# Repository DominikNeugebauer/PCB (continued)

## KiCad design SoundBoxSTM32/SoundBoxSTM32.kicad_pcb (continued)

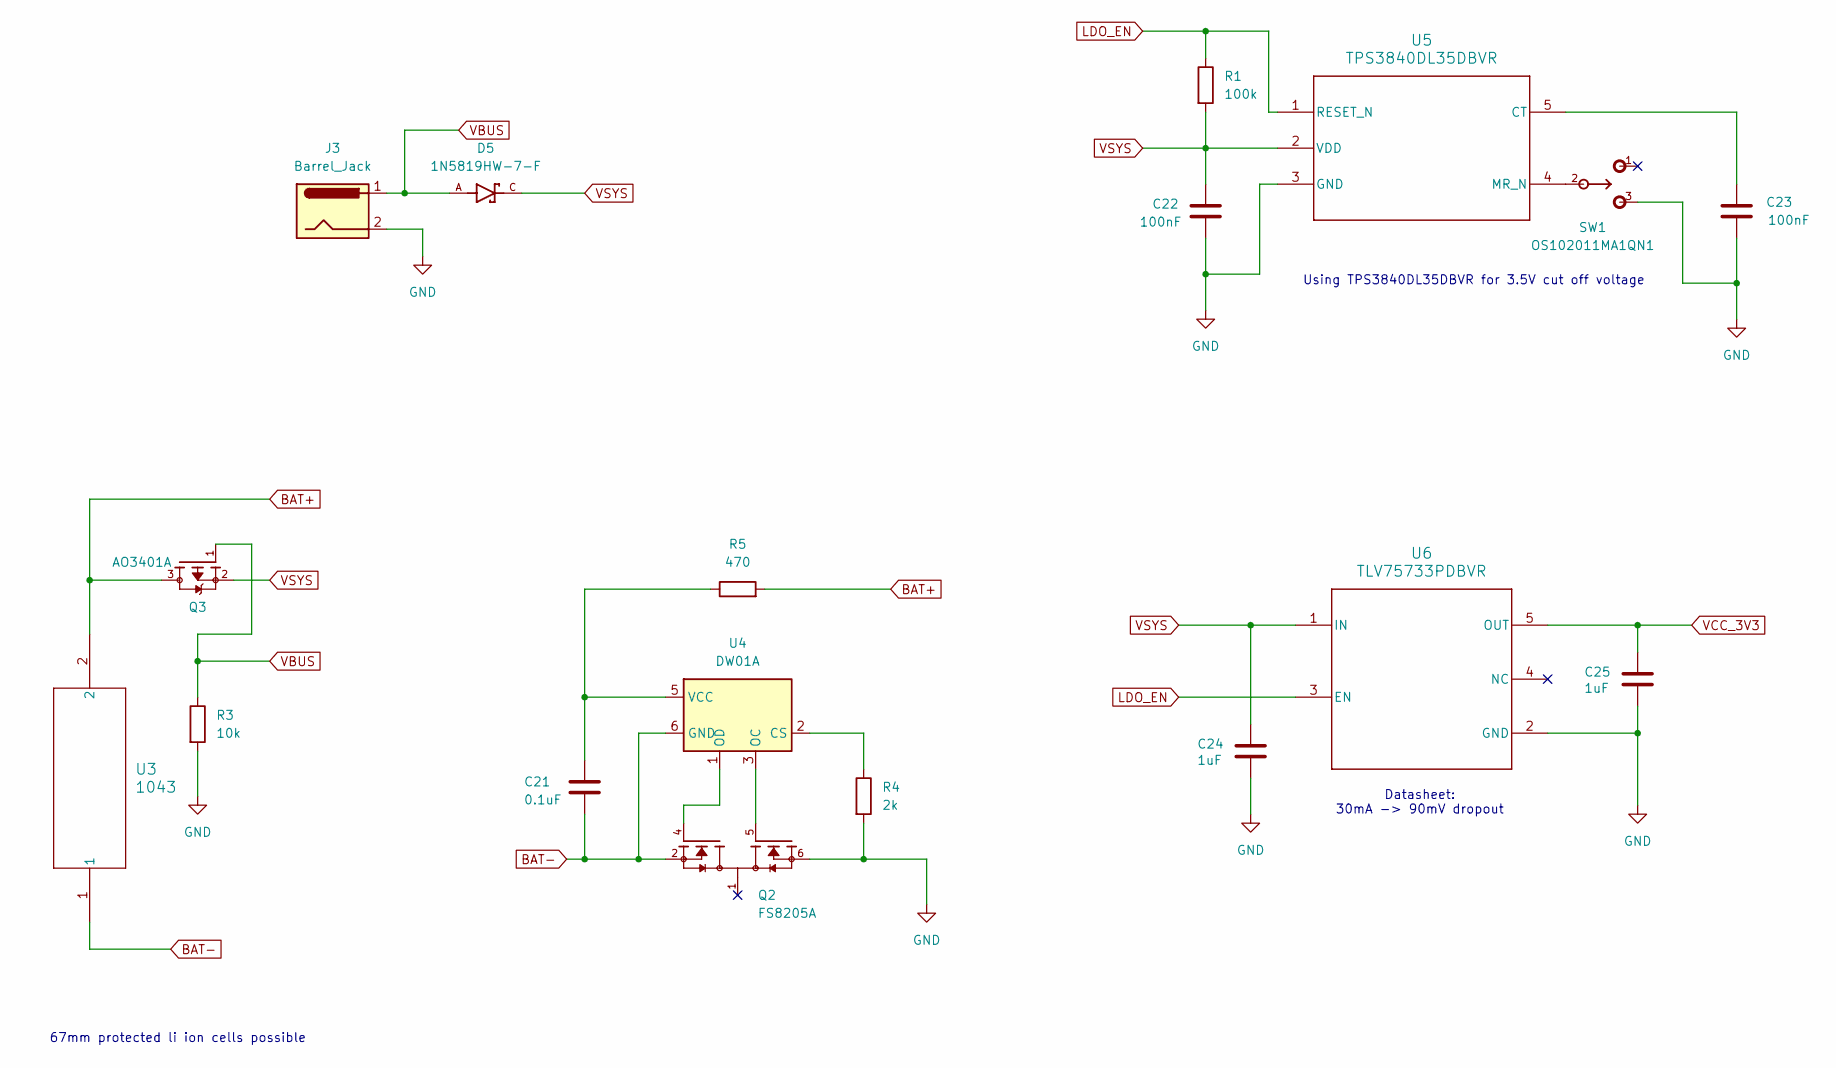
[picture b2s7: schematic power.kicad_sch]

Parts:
C21: 0.1uF; C_0603_1608Metric
C22, C23: 100nF; C_0603_1608Metric
C24, C25: 1uF; C_0603_1608Metric
D5: 1N5819HW-7-F; PARTREV 18-2
J3: Barrel_Jack; BarrelJack_Horizontal
Q2: FS8205A; PARTREV 1.7
Q3: AO3401A; PMOS-SOT23-3
R1: 100k; R_0603_1608Metric
R3: 10k; R_0603_1608Metric
R4: 2k; R_0603_1608Metric
R5: 470; R_0603_1608Metric
SW1: OS102011MA1QN1; MANUFACTURER_PART_NUMBER OS102011MA1QN1
U3: 1043; 1043_KEY
U4: DW01A; SOT-23-6
U5: TPS3840DL35DBVR; SOT-23-5
U6: TLV75733PDBVR; SOT95P280X145-5N_TLV75733PDBVR

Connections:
BAT+: Q3.3, R5.2, U3.2; also elsewhere on the board
BAT-: C21.2, Q2.2, Q2.3, U3.1, U4.6 (GND); also elsewhere on the board
GND: C22.2, C23.2, C24.2, C25.2, J3.2, Q2.6, Q2.7, R3.2, R4.2, SW1.3, U5.3 (GND), U6.2 (GND); also elsewhere on the board
LDO_EN: R1.1, U5.1 (RESET_N), U6.3 (EN)
unnamed: R4.1, U4.2 (CS)
unnamed: Q2.5, U4.3 (OC)
unnamed: Q2.4, U4.1 (OD)
unnamed: C21.1, R5.1, U4.5 (VCC)
unnamed: C23.1, U5.5 (CT)
unnamed: SW1.2, U5.4 (MR_N)
VBUS: D5.A, J3.1, Q3.1, R3.1
VCC_3V3: C25.1, U6.5 (OUT); also elsewhere on the board
VSYS: C22.1, C24.1, D5.C, Q3.2, R1.2, U5.2 (VDD), U6.1 (IN); also elsewhere on the board

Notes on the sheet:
Datasheet: 30mA -> 90mV dropout
67mm protected li ion cells possible
Using TPS3840DL35DBVR for 3.5V cut off voltage

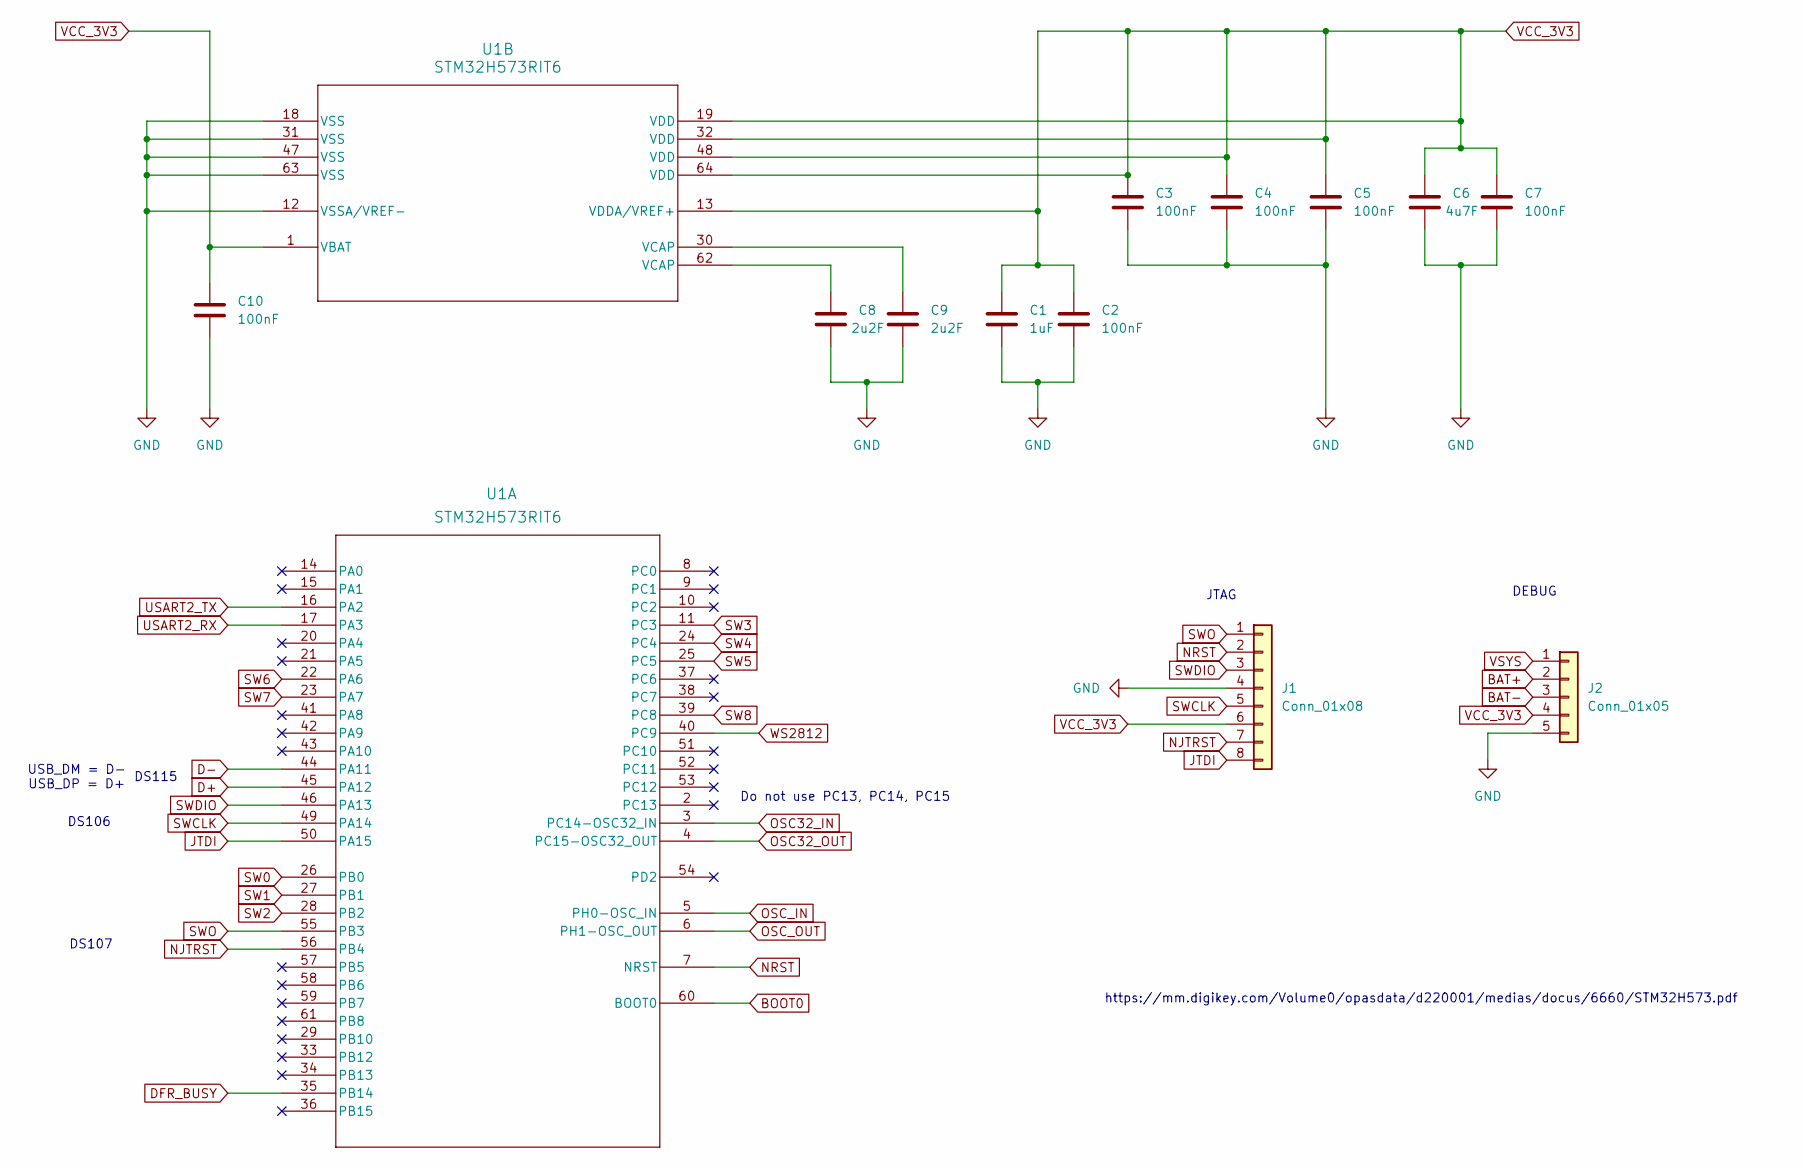
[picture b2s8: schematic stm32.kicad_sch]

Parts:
C1: 1uF; C_0603_1608Metric
C2, C3, C4, C5, C7, C10: 100nF; C_0603_1608Metric
C6: 4u7F; C_0603_1608Metric
C8, C9: 2u2F; C_0603_1608Metric
J1: Conn_01x08; PinHeader_1x08_P2.54mm_Vertical
J2: Conn_01x05; PinHeader_1x05_P2.54mm_Vertical
U1: STM32H573RIT6

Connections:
BAT+: J2.2; also elsewhere on the board
BAT-: J2.3; also elsewhere on the board
BOOT0: U1.60 (BOOT0); also elsewhere on the board
D+: U1.45 (PA12)
D-: U1.44 (PA11)
DFR_BUSY: U1.35 (PB14); also elsewhere on the board
GND: C1.2, C2.2, C3.2, C4.2, C5.2, C6.2, C7.2, C8.2, C9.2, C10.2, J1.4, J2.5, U1.12 (VSSA/VREF-), U1.18 (VSS), U1.31 (VSS), U1.47 (VSS), U1.63 (VSS); also elsewhere on the board
JTDI: J1.8, U1.50 (PA15)
NJTRST: J1.7, U1.56 (PB4)
NRST: J1.2, U1.7 (NRST); also elsewhere on the board
unnamed: C8.1, U1.62 (VCAP)
unnamed: C9.1, U1.30 (VCAP)
OSC32_IN: U1.3 (PC14-OSC32_IN); also elsewhere on the board
OSC32_OUT: U1.4 (PC15-OSC32_OUT); also elsewhere on the board
OSC_IN: U1.5 (PH0-OSC_IN); also elsewhere on the board
OSC_OUT: U1.6 (PH1-OSC_OUT); also elsewhere on the board
SW0: U1.26 (PB0); also elsewhere on the board
SW1: U1.27 (PB1); also elsewhere on the board
SW2: U1.28 (PB2); also elsewhere on the board
SW3: U1.11 (PC3); also elsewhere on the board
SW4: U1.24 (PC4); also elsewhere on the board
SW5: U1.25 (PC5); also elsewhere on the board
SW6: U1.22 (PA6); also elsewhere on the board
SW7: U1.23 (PA7); also elsewhere on the board
SW8: U1.39 (PC8); also elsewhere on the board
SWCLK: J1.5, U1.49 (PA14)
SWDIO: J1.3, U1.46 (PA13)
SWO: J1.1, U1.55 (PB3)
USART2_RX: U1.17 (PA3); also elsewhere on the board
USART2_TX: U1.16 (PA2); also elsewhere on the board
VCC_3V3: C1.1, C2.1, C3.1, C4.1, C5.1, C6.1, C7.1, C10.1, J1.6, J2.4, U1.1 (VBAT), U1.13 (VDDA/VREF+), U1.19 (VDD), U1.32 (VDD), U1.48 (VDD), U1.64 (VDD); also elsewhere on the board
VSYS: J2.1; also elsewhere on the board
WS2812: U1.40 (PC9); also elsewhere on the board

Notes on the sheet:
JTAG
DS106
https://mm.digikey.com/Volume0/opasdata/d220001/medias/docus/6660/STM32H573.pdf
DEBUG
Do not use PC13, PC14, PC15
DS115
DS107
USB_DM = D- USB_DP = D+

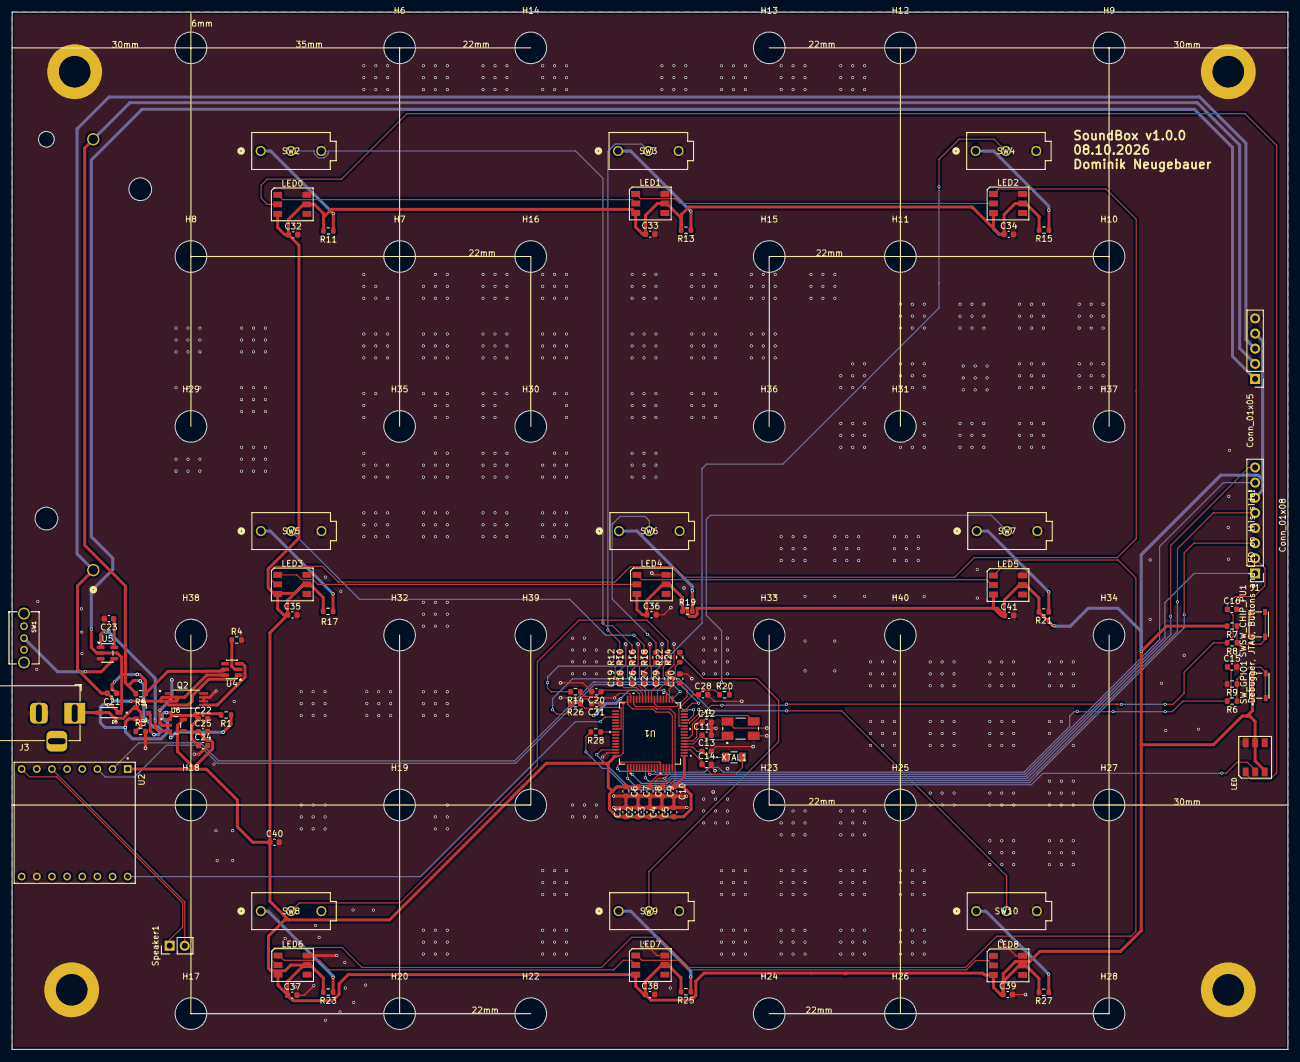
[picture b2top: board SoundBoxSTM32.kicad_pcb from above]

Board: 2 copper layers, 214.0 x 174.0 mm, 144 parts (1 on the bottom side), 71 nets.

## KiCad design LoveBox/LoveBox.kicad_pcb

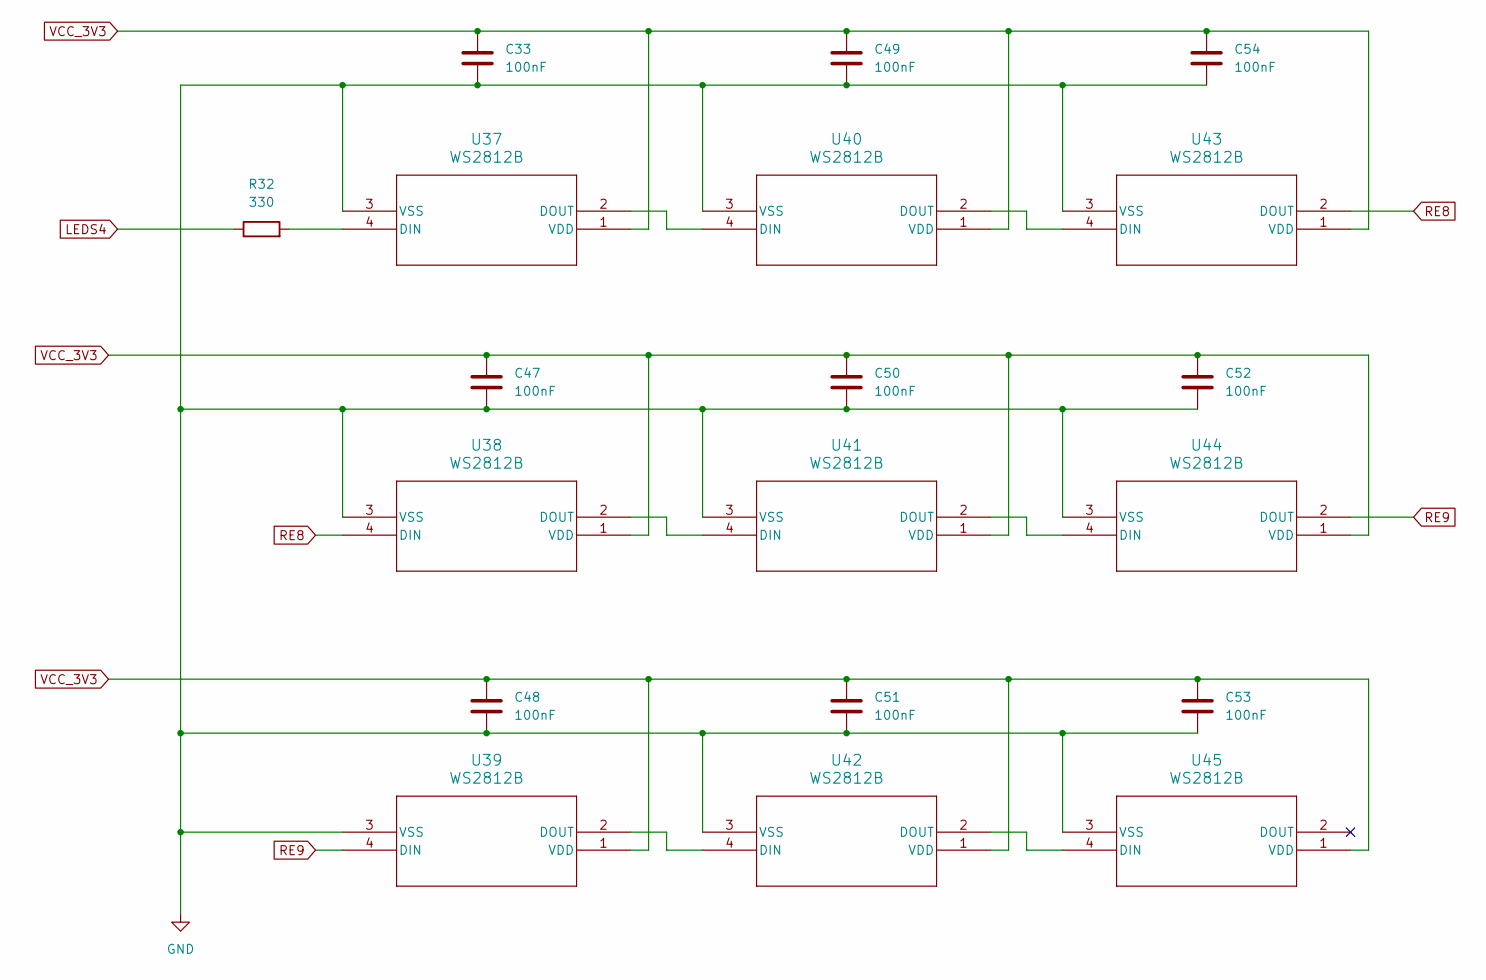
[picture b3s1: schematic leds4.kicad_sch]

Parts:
C33, C47, C48, C49, C50, C51, C52, C53, C54: 100nF; C_0603_1608Metric
R32: 330; R_0603_1608Metric
U37, U38, U39, U40, U41, U42, U43, U44, U45: WS2812B; WS2812B_WDS

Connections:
GND: C33.2, C47.2, C48.2, C49.2, C50.2, C51.2, C52.2, C53.2, C54.2, U37.3 (VSS), U38.3 (VSS), U39.3 (VSS), U40.3 (VSS), U41.3 (VSS), U42.3 (VSS), U43.3 (VSS), U44.3 (VSS), U45.3 (VSS); also elsewhere on the board
LEDS4: R32.1; also elsewhere on the board
unnamed: R32.2, U37.4 (DIN)
unnamed: U37.2 (DOUT), U40.4 (DIN)
unnamed: U38.2 (DOUT), U41.4 (DIN)
unnamed: U39.2 (DOUT), U42.4 (DIN)
unnamed: U40.2 (DOUT), U43.4 (DIN)
unnamed: U41.2 (DOUT), U44.4 (DIN)
unnamed: U42.2 (DOUT), U45.4 (DIN)
RE8: U38.4 (DIN), U43.2 (DOUT)
RE9: U39.4 (DIN), U44.2 (DOUT)
VCC_3V3: C33.1, C47.1, C48.1, C49.1, C50.1, C51.1, C52.1, C53.1, C54.1, U37.1 (VDD), U38.1 (VDD), U39.1 (VDD), U40.1 (VDD), U41.1 (VDD), U42.1 (VDD), U43.1 (VDD), U44.1 (VDD), U45.1 (VDD); also elsewhere on the board

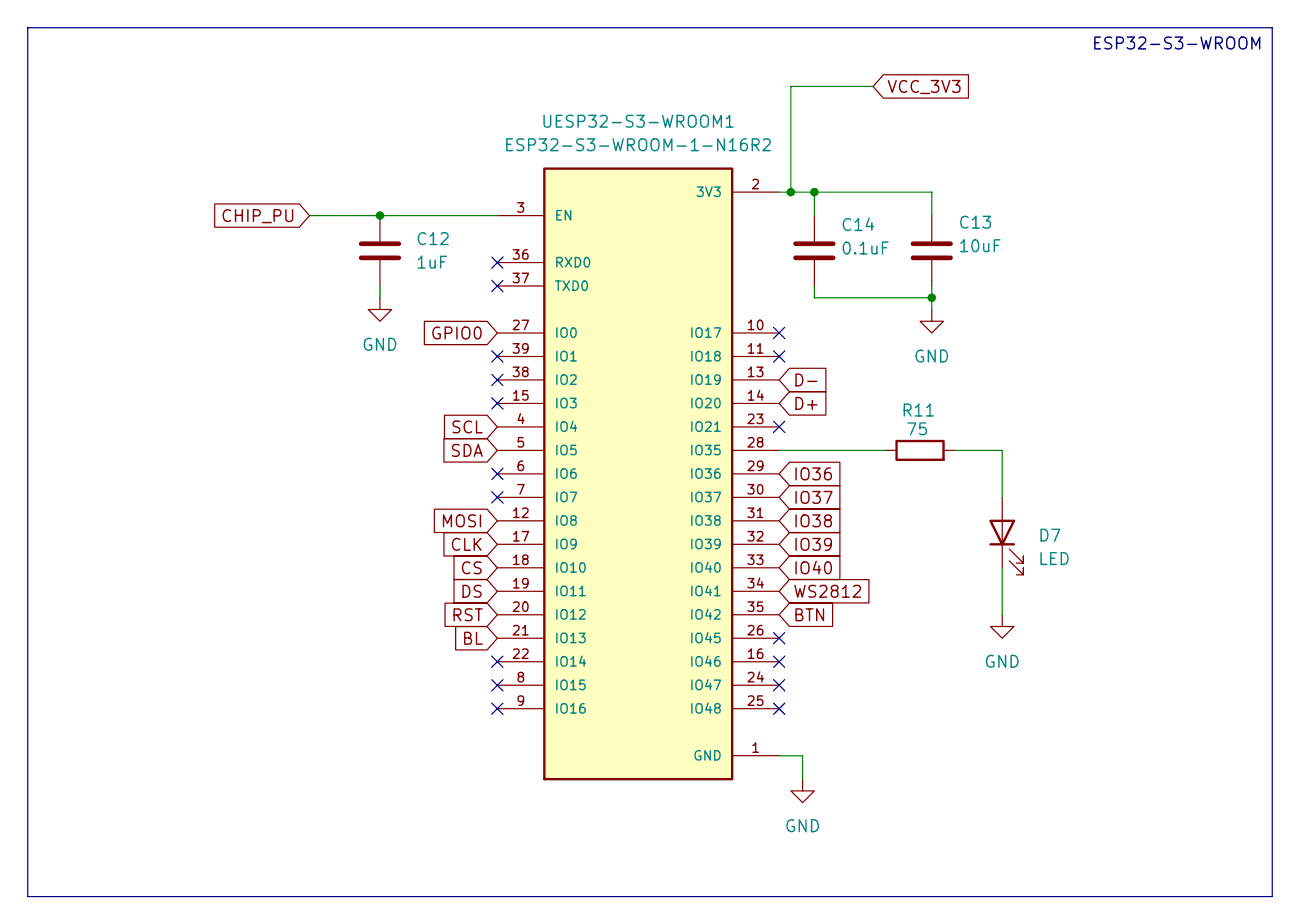
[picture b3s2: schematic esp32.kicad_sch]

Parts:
C12: 1uF; C_0603_1608Metric
C13: 10uF; C_0603_1608Metric
C14: 0.1uF; C_0603_1608Metric
D7: LED; LED_1206_3216Metric
R11: 75; R_0603_1608Metric
UESP32-S3-WROOM1: ESP32-S3-WROOM-1-N16R2; PARTREV v1.0

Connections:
BL: UESP32-S3-WROOM1.21 (IO13)
BTN: UESP32-S3-WROOM1.35 (IO42); also elsewhere on the board
CHIP_PU: C12.1, UESP32-S3-WROOM1.3 (EN); also elsewhere on the board
CLK: UESP32-S3-WROOM1.17 (IO9)
CS: UESP32-S3-WROOM1.18 (IO10)
D+: UESP32-S3-WROOM1.14 (IO20); also elsewhere on the board
D-: UESP32-S3-WROOM1.13 (IO19); also elsewhere on the board
DS: UESP32-S3-WROOM1.19 (IO11)
GND: C12.2, C13.2, C14.2, D7.1 (K), UESP32-S3-WROOM1.1 (GND), UESP32-S3-WROOM1.40 (GND), UESP32-S3-WROOM1.41_1 (GND), UESP32-S3-WROOM1.41_2 (GND), UESP32-S3-WROOM1.41_3 (GND), UESP32-S3-WROOM1.41_4 (GND), UESP32-S3-WROOM1.41_5 (GND), UESP32-S3-WROOM1.41_6 (GND), UESP32-S3-WROOM1.41_7 (GND), UESP32-S3-WROOM1.41_8 (GND), UESP32-S3-WROOM1.41_9 (GND), UESP32-S3-WROOM1.41_10, UESP32-S3-WROOM1.41_11, UESP32-S3-WROOM1.41_12, UESP32-S3-WROOM1.41_13, UESP32-S3-WROOM1.41_14, UESP32-S3-WROOM1.41_15, UESP32-S3-WROOM1.41_16, UESP32-S3-WROOM1.41_17, UESP32-S3-WROOM1.41_18, UESP32-S3-WROOM1.41_19, UESP32-S3-WROOM1.41_20, UESP32-S3-WROOM1.41_21; also elsewhere on the board
GPIO0: UESP32-S3-WROOM1.27 (IO0); also elsewhere on the board
IO36: UESP32-S3-WROOM1.29 (IO36)
IO37: UESP32-S3-WROOM1.30 (IO37)
IO38: UESP32-S3-WROOM1.31 (IO38)
IO39: UESP32-S3-WROOM1.32 (IO39)
IO40: UESP32-S3-WROOM1.33 (IO40)
MOSI: UESP32-S3-WROOM1.12 (IO8)
unnamed: D7.2 (A), R11.2
unnamed: R11.1, UESP32-S3-WROOM1.28 (IO35)
RST: UESP32-S3-WROOM1.20 (IO12)
SCL: UESP32-S3-WROOM1.4 (IO4)
SDA: UESP32-S3-WROOM1.5 (IO5)
VCC_3V3: C13.1, C14.1, UESP32-S3-WROOM1.2 (3V3); also elsewhere on the board
WS2812: UESP32-S3-WROOM1.34 (IO41); also elsewhere on the board

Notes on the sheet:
ESP32-S3-WROOM

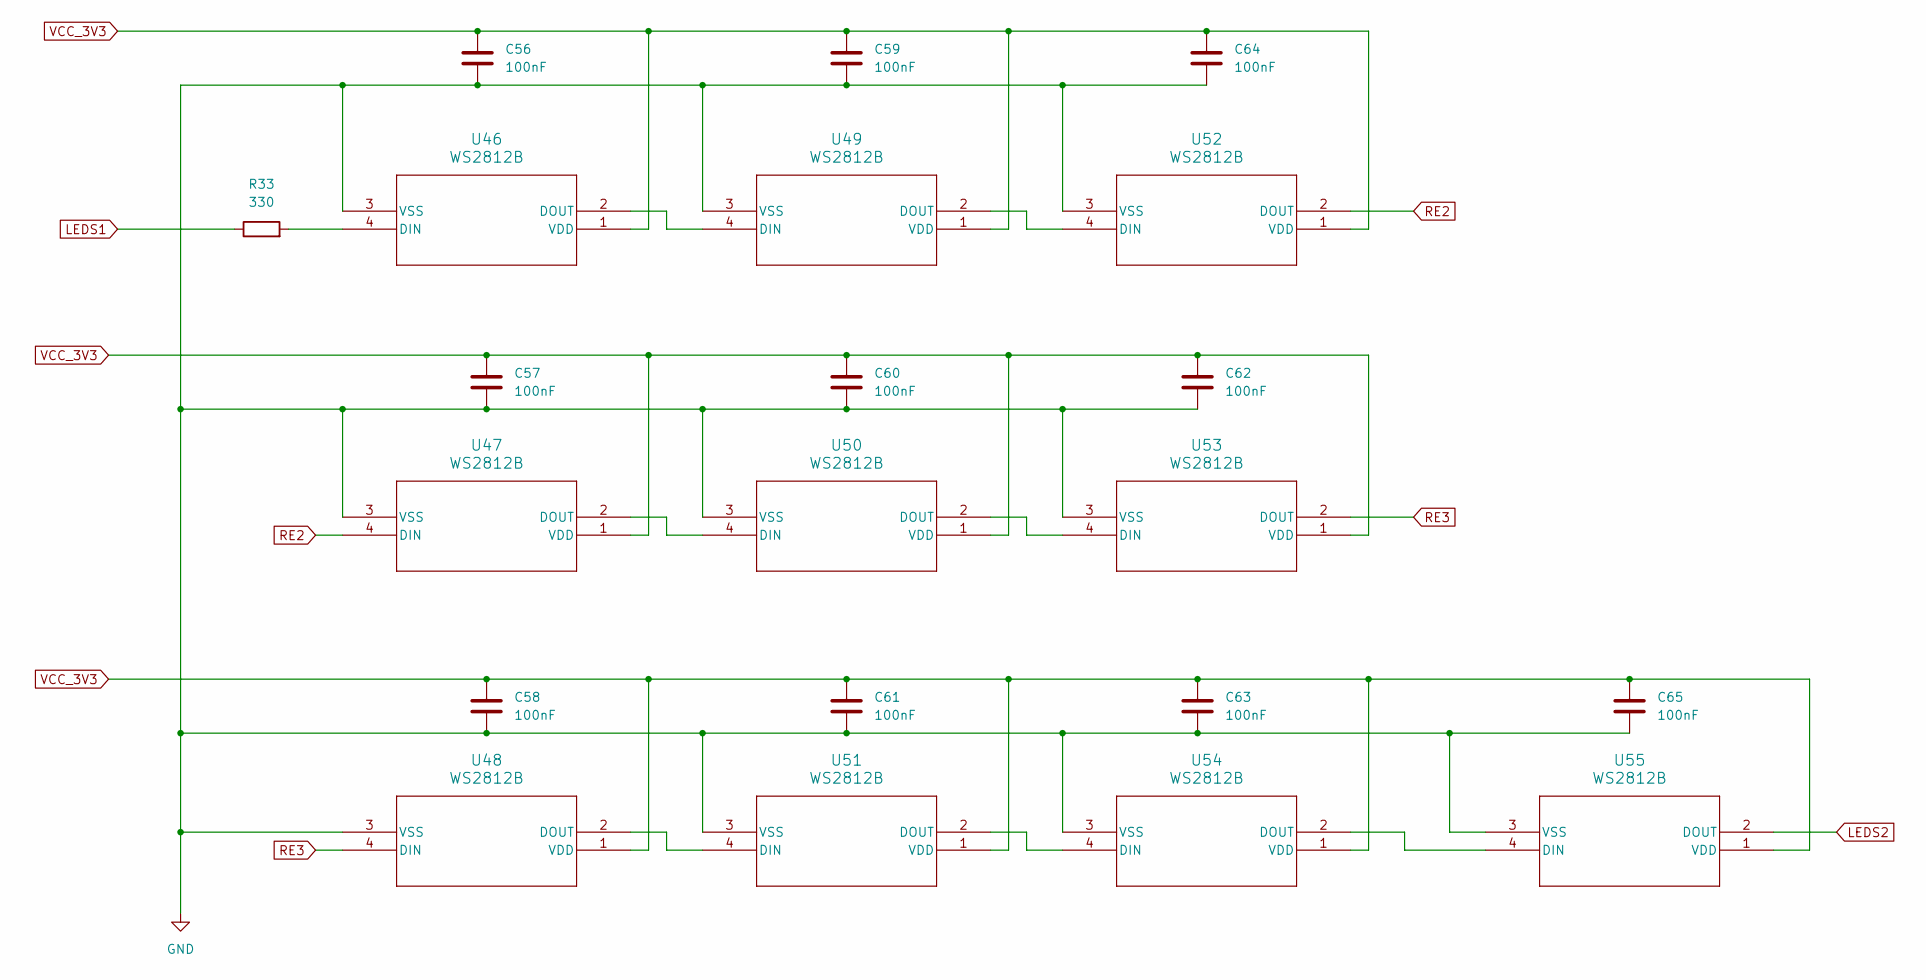
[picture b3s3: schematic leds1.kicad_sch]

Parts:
C56, C57, C58, C59, C60, C61, C62, C63, C64, C65: 100nF; C_0603_1608Metric
R33: 330; R_0603_1608Metric
U46, U47, U48, U49, U50, U51, U52, U53, U54, U55: WS2812B; WS2812B_WDS

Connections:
GND: C56.2, C57.2, C58.2, C59.2, C60.2, C61.2, C62.2, C63.2, C64.2, C65.2, U46.3 (VSS), U47.3 (VSS), U48.3 (VSS), U49.3 (VSS), U50.3 (VSS), U51.3 (VSS), U52.3 (VSS), U53.3 (VSS), U54.3 (VSS), U55.3 (VSS); also elsewhere on the board
LEDS1: R33.1; also elsewhere on the board
LEDS2: U55.2 (DOUT); also elsewhere on the board
unnamed: R33.2, U46.4 (DIN)
unnamed: U46.2 (DOUT), U49.4 (DIN)
unnamed: U47.2 (DOUT), U50.4 (DIN)
unnamed: U48.2 (DOUT), U51.4 (DIN)
unnamed: U49.2 (DOUT), U52.4 (DIN)
unnamed: U50.2 (DOUT), U53.4 (DIN)
unnamed: U51.2 (DOUT), U54.4 (DIN)
unnamed: U54.2 (DOUT), U55.4 (DIN)
RE2: U47.4 (DIN), U52.2 (DOUT)
RE3: U48.4 (DIN), U53.2 (DOUT)
VCC_3V3: C56.1, C57.1, C58.1, C59.1, C60.1, C61.1, C62.1, C63.1, C64.1, C65.1, U46.1 (VDD), U47.1 (VDD), U48.1 (VDD), U49.1 (VDD), U50.1 (VDD), U51.1 (VDD), U52.1 (VDD), U53.1 (VDD), U54.1 (VDD), U55.1 (VDD); also elsewhere on the board

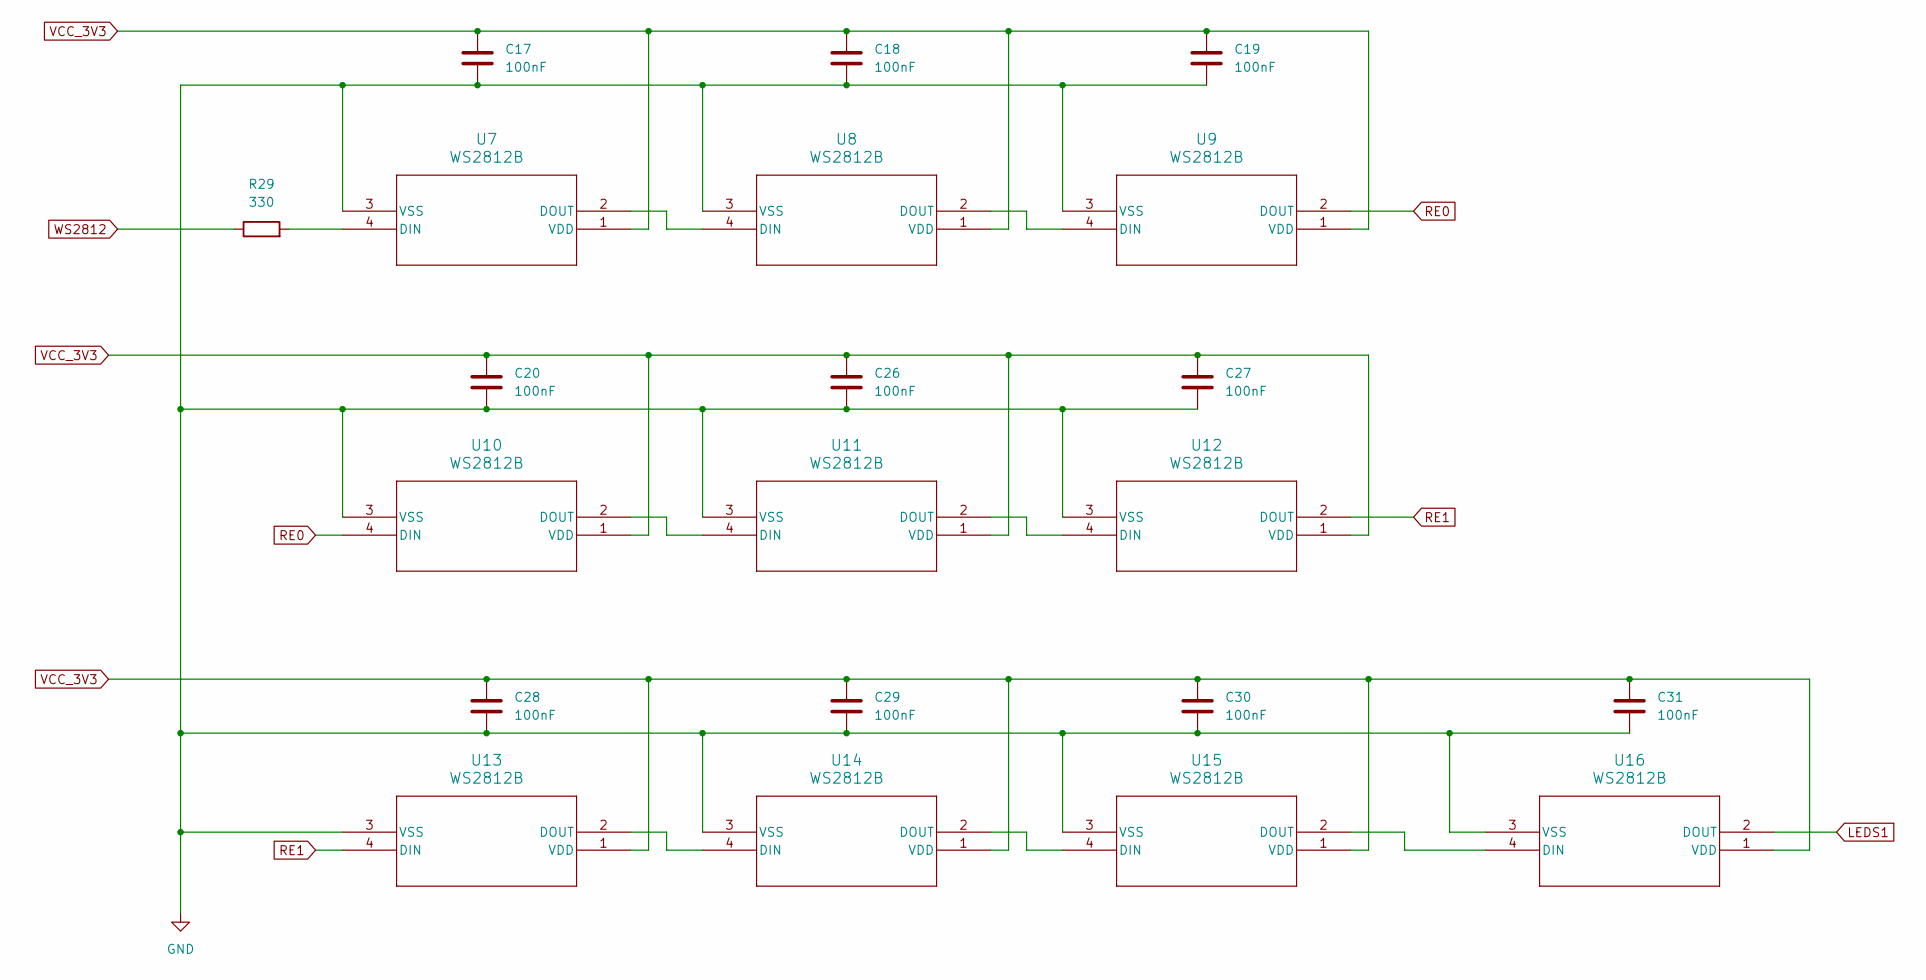
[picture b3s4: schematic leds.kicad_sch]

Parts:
C17, C18, C19, C20, C26, C27, C28, C29, C30, C31: 100nF; C_0603_1608Metric
R29: 330; R_0603_1608Metric
U7, U8, U9, U10, U11, U12, U13, U14, U15, U16: WS2812B; WS2812B_WDS

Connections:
GND: C17.2, C18.2, C19.2, C20.2, C26.2, C27.2, C28.2, C29.2, C30.2, C31.2, U7.3 (VSS), U8.3 (VSS), U9.3 (VSS), U10.3 (VSS), U11.3 (VSS), U12.3 (VSS), U13.3 (VSS), U14.3 (VSS), U15.3 (VSS), U16.3 (VSS); also elsewhere on the board
LEDS1: U16.2 (DOUT); also elsewhere on the board
unnamed: R29.2, U7.4 (DIN)
unnamed: U7.2 (DOUT), U8.4 (DIN)
unnamed: U8.2 (DOUT), U9.4 (DIN)
unnamed: U10.2 (DOUT), U11.4 (DIN)
unnamed: U11.2 (DOUT), U12.4 (DIN)
unnamed: U13.2 (DOUT), U14.4 (DIN)
unnamed: U14.2 (DOUT), U15.4 (DIN)
unnamed: U15.2 (DOUT), U16.4 (DIN)
RE0: U9.2 (DOUT), U10.4 (DIN)
RE1: U12.2 (DOUT), U13.4 (DIN)
VCC_3V3: C17.1, C18.1, C19.1, C20.1, C26.1, C27.1, C28.1, C29.1, C30.1, C31.1, U7.1 (VDD), U8.1 (VDD), U9.1 (VDD), U10.1 (VDD), U11.1 (VDD), U12.1 (VDD), U13.1 (VDD), U14.1 (VDD), U15.1 (VDD), U16.1 (VDD); also elsewhere on the board
WS2812: R29.1; also elsewhere on the board

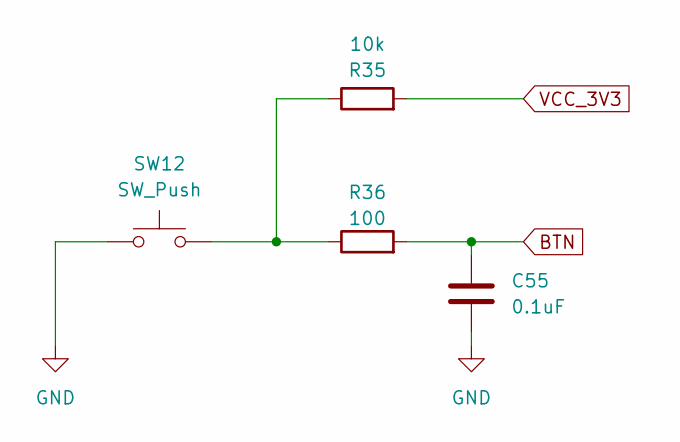
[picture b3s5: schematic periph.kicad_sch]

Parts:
C55: 0.1uF; C_0603_1608Metric
R35: 10k; R_0603_1608Metric
R36: 100; R_0603_1608Metric
SW12: SW_Push; SW_Cherry_MX_1.00u_PCB

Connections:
BTN: C55.1, R36.2; also elsewhere on the board
GND: C55.2, SW12.1; also elsewhere on the board
unnamed: R35.1, R36.1, SW12.2
VCC_3V3: R35.2; also elsewhere on the board

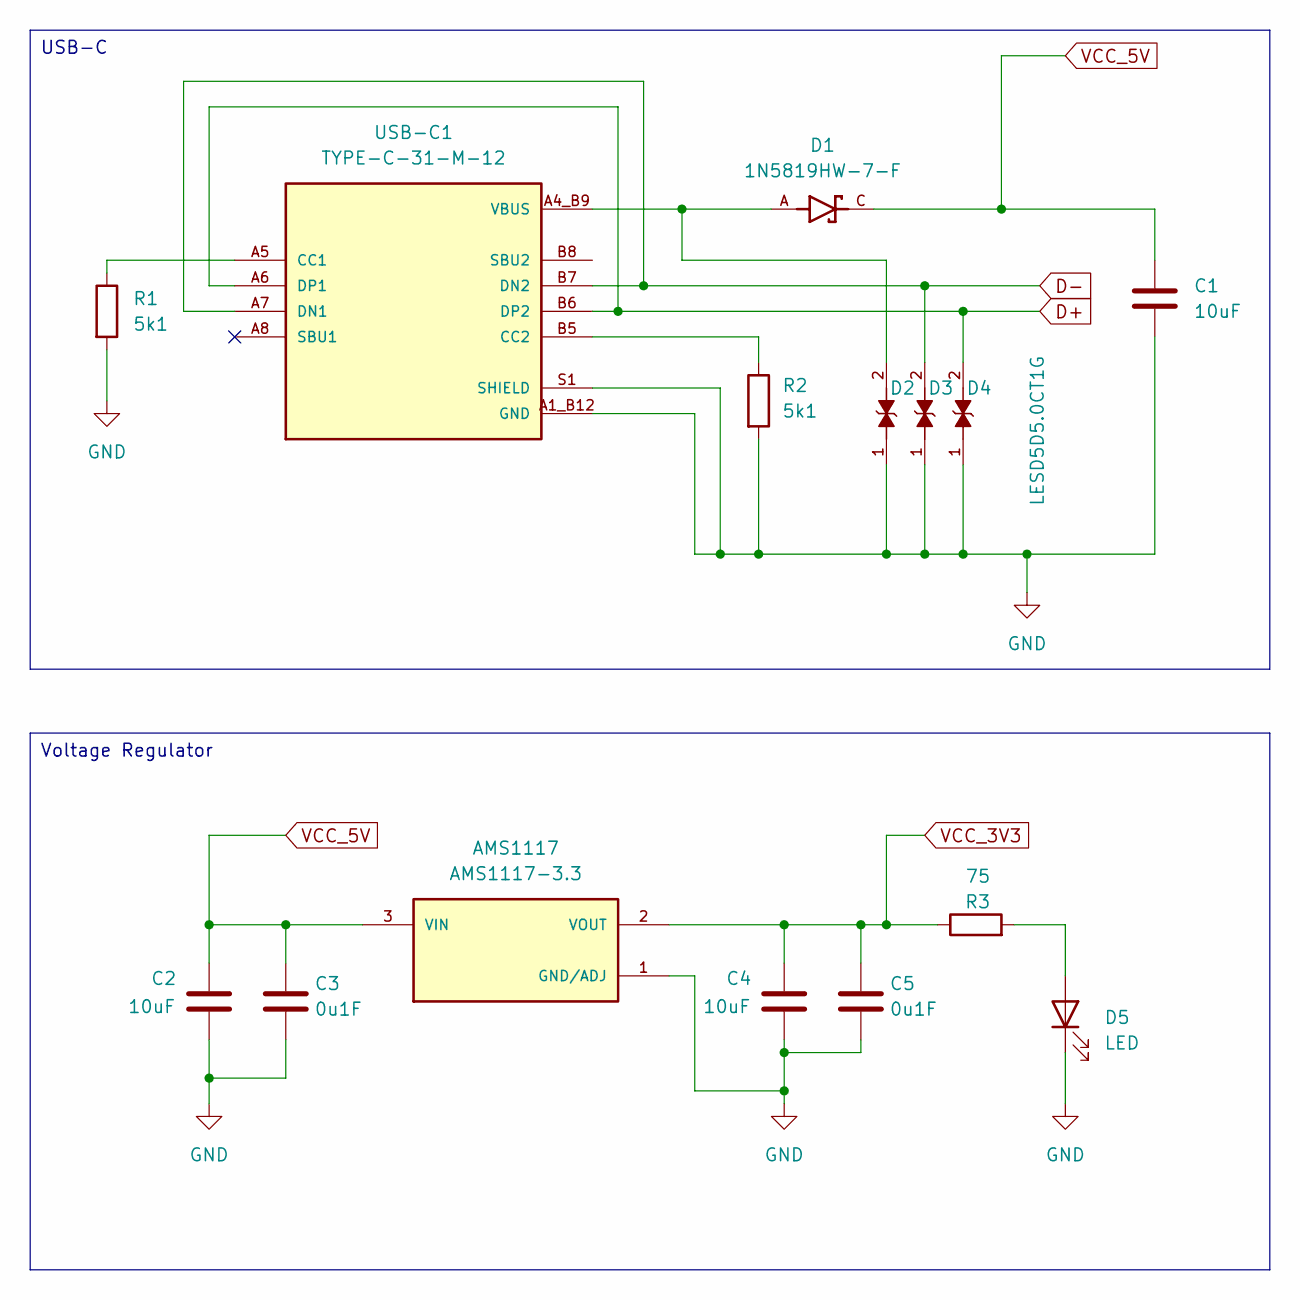
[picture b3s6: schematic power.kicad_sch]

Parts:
AMS1117: AMS1117-3.3; SOT-223-3_TabPin2; PARTREV N/A
C1, C2, C4: 10uF; C_0603_1608Metric
C3, C5: 0u1F; C_0603_1608Metric
D1: 1N5819HW-7-F; PARTREV 18-2
D2, D3, D4: LESD5D5.0CT1G; PARTREV O
D5: LED; LED_1206_3216Metric
R1, R2: 5k1; R_0603_1608Metric
R3: 75; R_0603_1608Metric
USB-C1: TYPE-C-31-M-12; PARTREV 2020.12.08

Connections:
D+: D4.2, USB-C1.A6 (DP1), USB-C1.B6 (DP2); also elsewhere on the board
D-: D3.2, USB-C1.A7 (DN1), USB-C1.B7 (DN2); also elsewhere on the board
GND: AMS1117.1 (GND/ADJ), C1.2, C2.2, C3.2, C4.2, C5.2, D2.1, D3.1, D4.1, D5.1 (K), R1.2, R2.2, USB-C1.A1_B12 (GND), USB-C1.B1_A12 (GND), USB-C1.S1 (SHIELD), USB-C1.S2 (SHIELD), USB-C1.S3 (SHIELD), USB-C1.S4 (SHIELD); also elsewhere on the board
unnamed: D5.2 (A), R3.2
unnamed: R1.1, USB-C1.A5 (CC1)
unnamed: R2.1, USB-C1.B5 (CC2)
VBUS: D1.A, D2.2, USB-C1.A4_B9 (VBUS), USB-C1.B4_A9 (VBUS)
VCC_3V3: AMS1117.2 (VOUT), C4.1, C5.1, R3.1; also elsewhere on the board
VCC_5V: AMS1117.3 (VIN), C1.1, C2.1, C3.1, D1.C

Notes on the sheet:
Voltage Regulator
USB-C

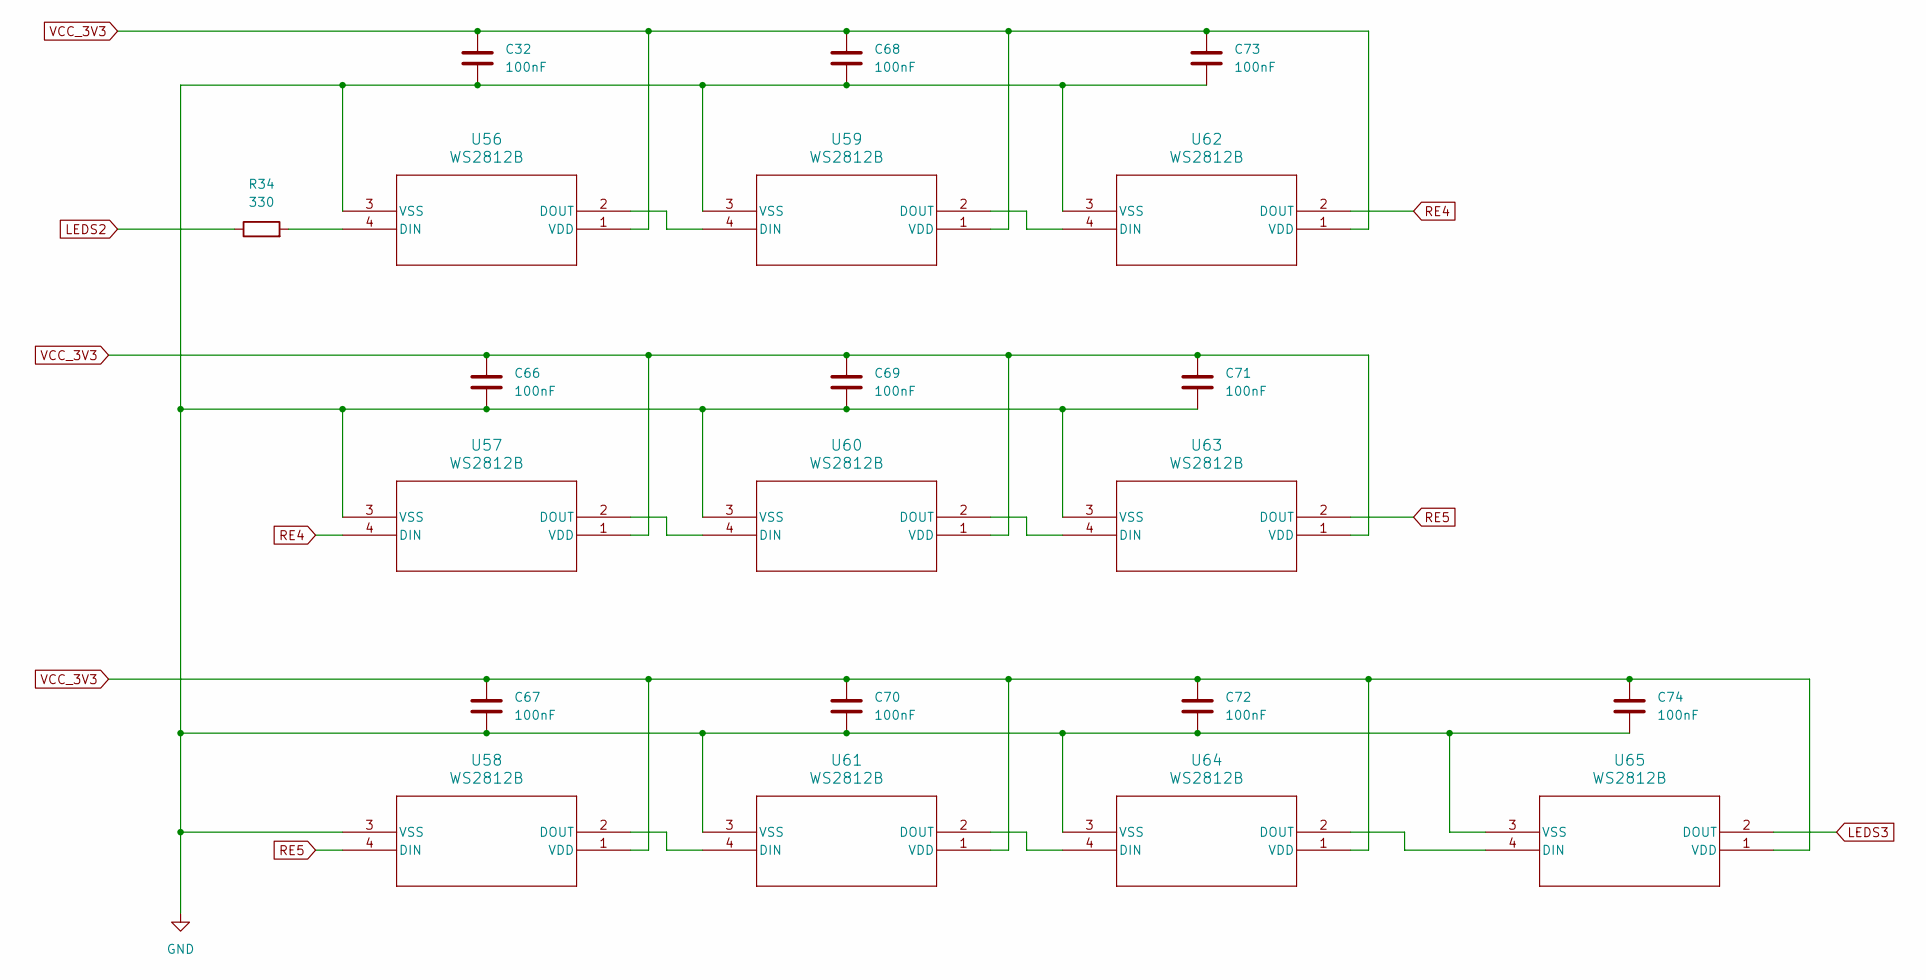
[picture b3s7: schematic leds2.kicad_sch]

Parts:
C32, C66, C67, C68, C69, C70, C71, C72, C73, C74: 100nF; C_0603_1608Metric
R34: 330; R_0603_1608Metric
U56, U57, U58, U59, U60, U61, U62, U63, U64, U65: WS2812B; WS2812B_WDS

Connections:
GND: C32.2, C66.2, C67.2, C68.2, C69.2, C70.2, C71.2, C72.2, C73.2, C74.2, U56.3 (VSS), U57.3 (VSS), U58.3 (VSS), U59.3 (VSS), U60.3 (VSS), U61.3 (VSS), U62.3 (VSS), U63.3 (VSS), U64.3 (VSS), U65.3 (VSS); also elsewhere on the board
LEDS2: R34.1; also elsewhere on the board
LEDS3: U65.2 (DOUT); also elsewhere on the board
unnamed: R34.2, U56.4 (DIN)
unnamed: U56.2 (DOUT), U59.4 (DIN)
unnamed: U57.2 (DOUT), U60.4 (DIN)
unnamed: U58.2 (DOUT), U61.4 (DIN)
unnamed: U59.2 (DOUT), U62.4 (DIN)
unnamed: U60.2 (DOUT), U63.4 (DIN)
unnamed: U61.2 (DOUT), U64.4 (DIN)
unnamed: U64.2 (DOUT), U65.4 (DIN)
RE4: U57.4 (DIN), U62.2 (DOUT)
RE5: U58.4 (DIN), U63.2 (DOUT)
VCC_3V3: C32.1, C66.1, C67.1, C68.1, C69.1, C70.1, C71.1, C72.1, C73.1, C74.1, U56.1 (VDD), U57.1 (VDD), U58.1 (VDD), U59.1 (VDD), U60.1 (VDD), U61.1 (VDD), U62.1 (VDD), U63.1 (VDD), U64.1 (VDD), U65.1 (VDD); also elsewhere on the board
